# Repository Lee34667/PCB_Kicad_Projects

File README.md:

Contains some the PCB projects I have done using KiCad. Most of this boards have been used in the industries and research work.

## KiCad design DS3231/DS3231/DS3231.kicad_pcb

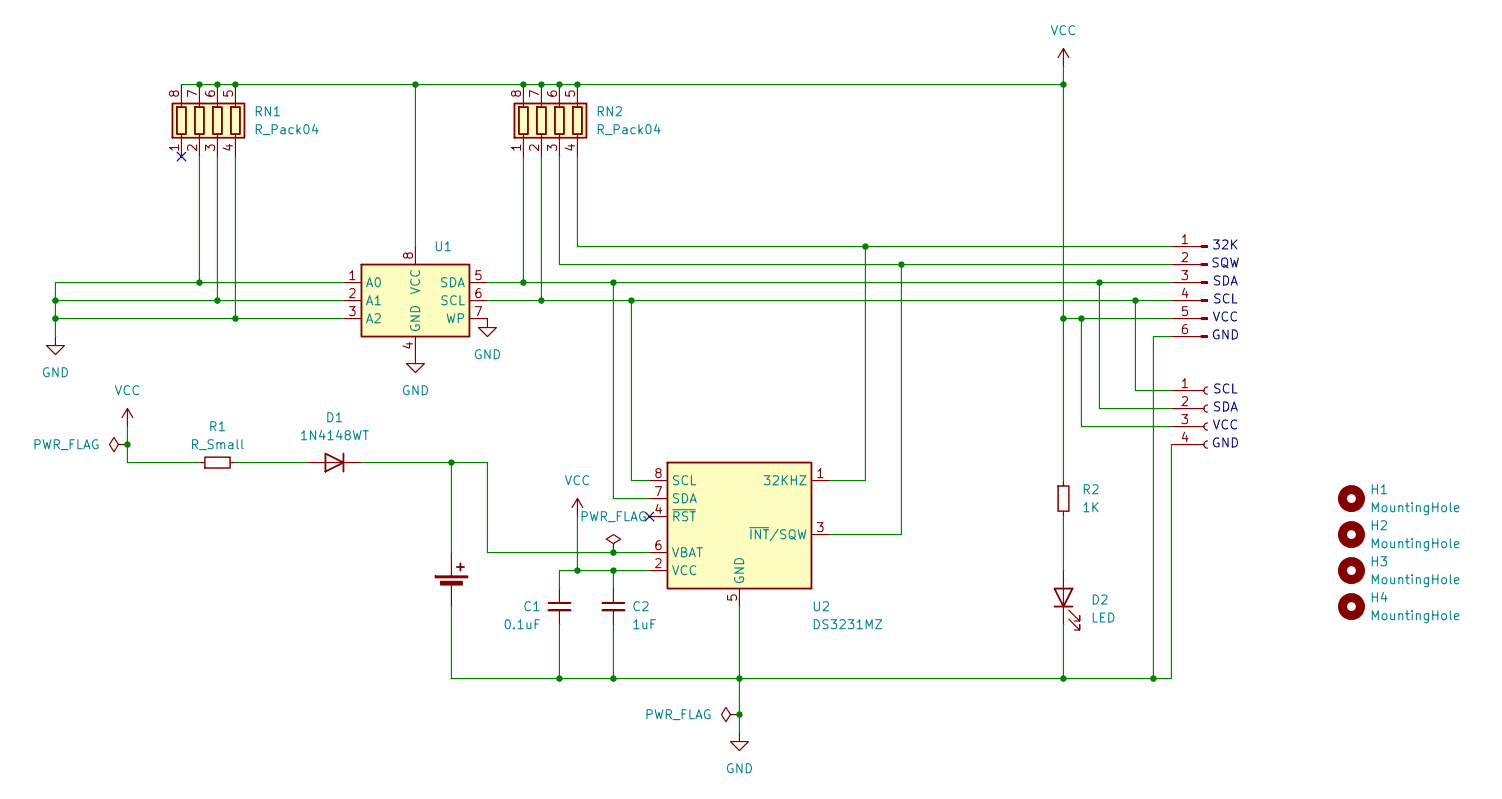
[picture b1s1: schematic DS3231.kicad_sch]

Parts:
BT1: Battery_Cell; BatteryHolder_Keystone_103_1x20mm
C1: 0.1uF; C_0805_2012Metric_Pad1.18x1.45mm_HandSolder
C2: 1uF; C_0805_2012Metric_Pad1.18x1.45mm_HandSolder
D1: 1N4148WT; D_1206_3216Metric_Pad1.42x1.75mm_HandSolder
D2: LED; LED_0805_2012Metric_Pad1.15x1.40mm_HandSolder
H1, H2, H3, H4: MountingHole; MountingHole_2.1mm
J1: Conn_01x06_Pin; PinHeader_1x06_P2.54mm_Horizontal
J2: Conn_01x04_Socket; PinHeader_1x04_P2.54mm_Vertical
R1: R_Small; R_0805_2012Metric_Pad1.20x1.40mm_HandSolder
R2: 1K; R_0805_2012Metric_Pad1.20x1.40mm_HandSolder
RN1, RN2: R_Pack04; R_Array_Convex_4x0603
U1: AT24CS32-SSHM; SOIC-8_3.9x4.9mm_P1.27mm
U2: DS3231MZ; SO-8_5.3x6.2mm_P1.27mm

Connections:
GND: BT1.2 (-), C1.2, C2.2, D2.1 (K), J1.6, J2.4, RN1.2 (R2.1), RN1.3 (R3.1), RN1.4 (R4.1), U1.1 (A0), U1.2 (A1), U1.3 (A2), U1.4 (GND), U1.7 (WP), U2.5 (GND)
unnamed: BT1.1 (+), D1.1 (K), U2.6 (VBAT)
unnamed: D1.2 (A), R1.2
unnamed: D2.2 (A), R2.2
unnamed: J1.1, RN2.4 (R4.1), U2.1 (32KHZ)
unnamed: J1.2, RN2.3 (R3.1), U2.3 (~INT/SQW)
unnamed: J1.3, J2.2, RN2.1 (R1.1), U1.5 (SDA), U2.7 (SDA)
unnamed: J1.4, J2.1, RN2.2 (R2.1), U1.6 (SCL), U2.8 (SCL)
VCC: C1.1, C2.1, J1.5, J2.3, R1.1, R2.1, RN1.5 (R4.2), RN1.6 (R3.2), RN1.7 (R2.2), RN1.8 (R1.2), RN2.5 (R4.2), RN2.6 (R3.2), RN2.7 (R2.2), RN2.8 (R1.2), U1.8 (VCC), U2.2 (VCC)

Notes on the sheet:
SCL
GND
SDA
VCC
SQW
VCC
32K
GND

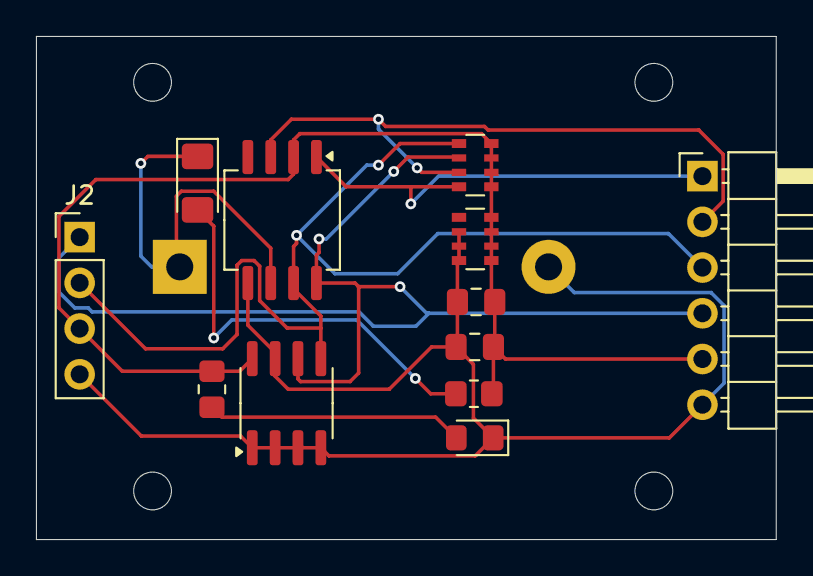
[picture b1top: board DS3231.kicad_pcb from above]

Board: 2 copper layers, 41.1 x 27.9 mm, 17 parts (1 on the bottom side), 9 nets.

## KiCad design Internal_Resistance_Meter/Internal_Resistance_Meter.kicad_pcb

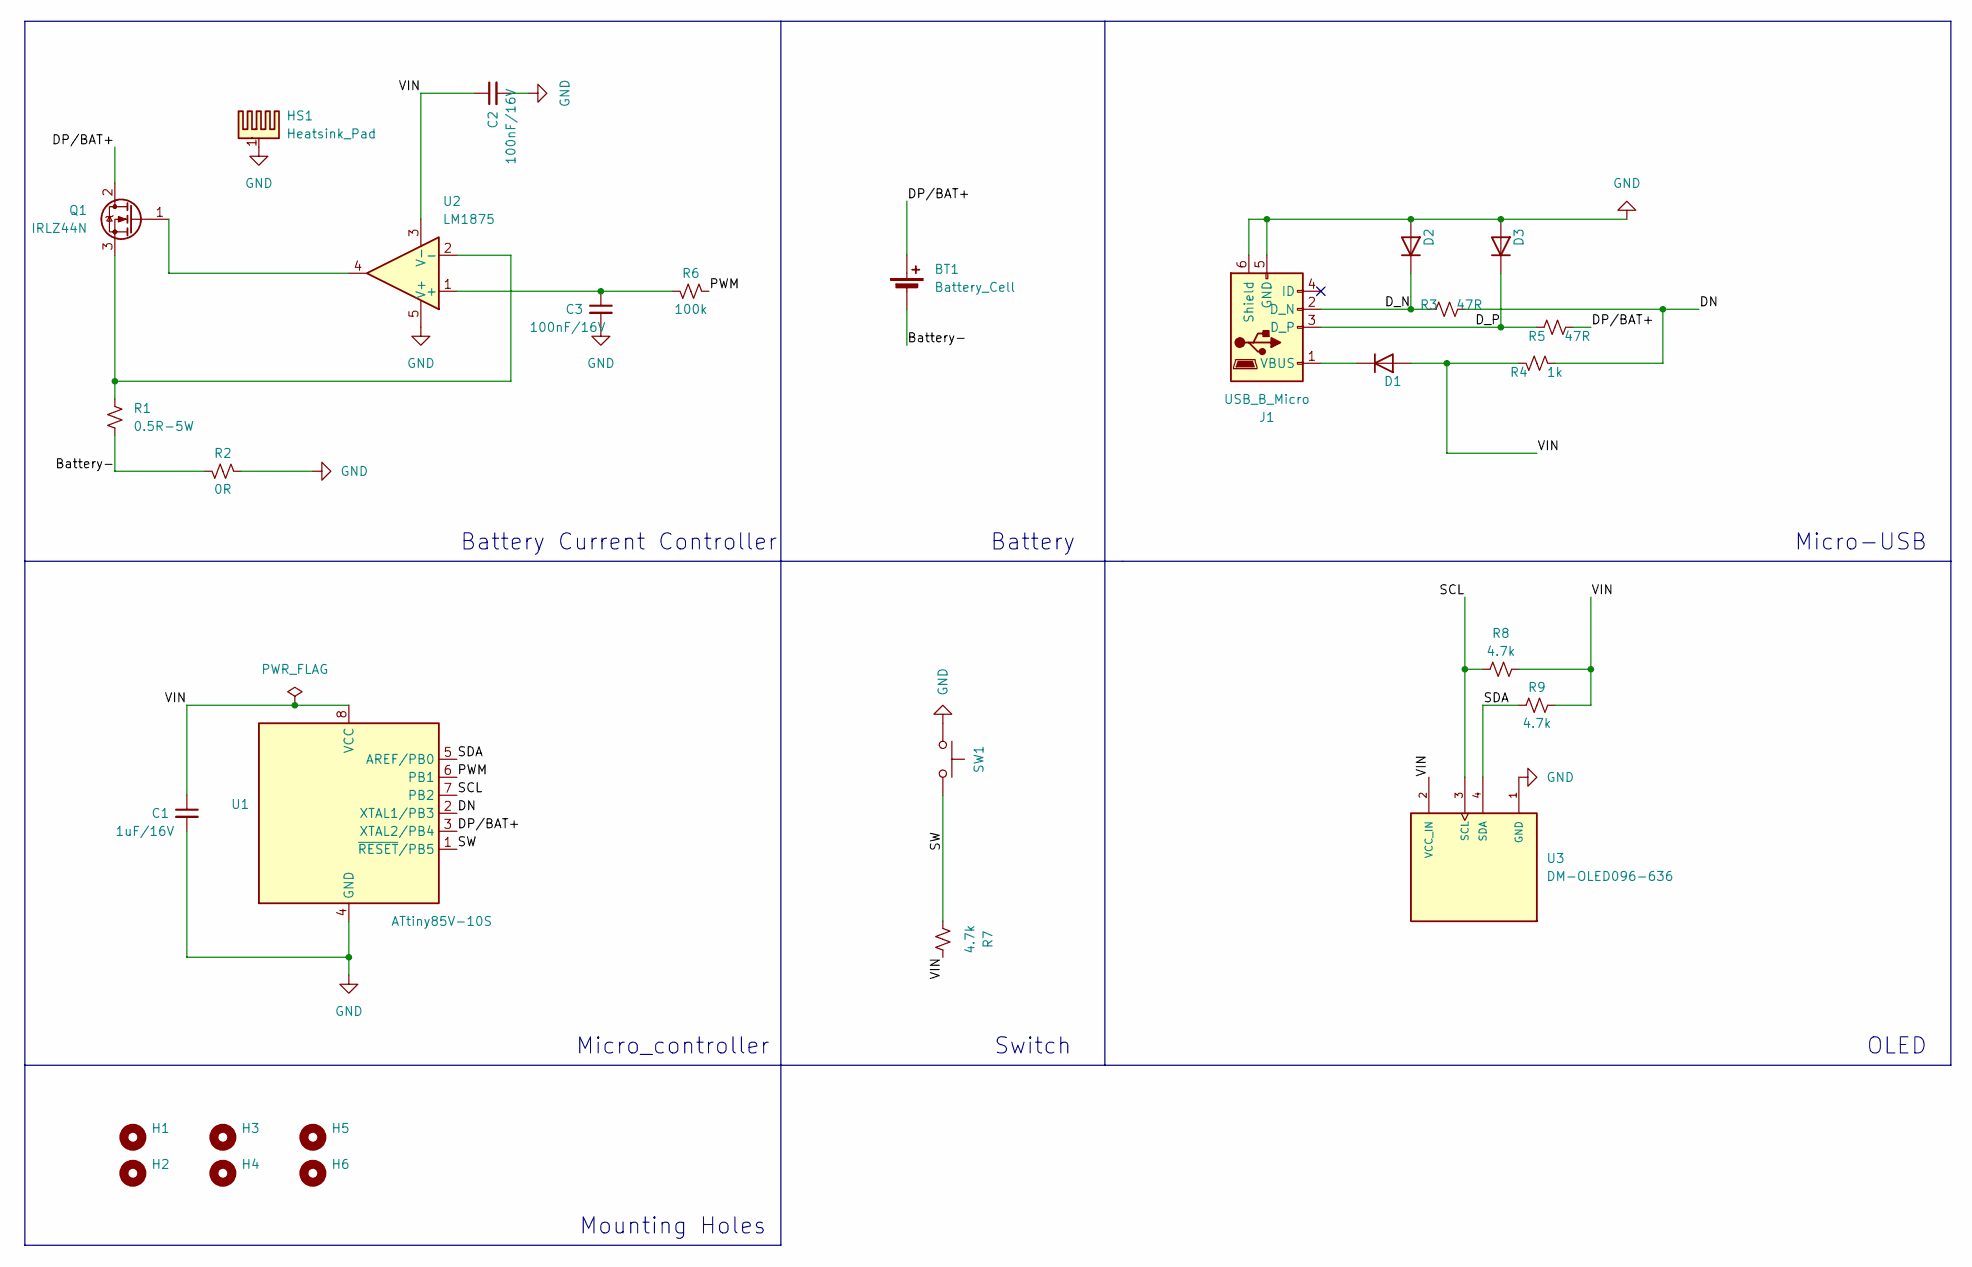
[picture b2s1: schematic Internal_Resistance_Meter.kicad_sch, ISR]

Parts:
BT1: Battery_Cell; BatteryHolder_MPD_BH-18650-PC2
C1: 1uF/16V; C_1210_3225Metric_Pad1.33x2.70mm_HandSolder
C2, C3: 100nF/16V; C_1210_3225Metric_Pad1.33x2.70mm_HandSolder
D1, D2, D3: 1N4148WT; D_SOD-523
H1, H2, H3, H4, H5, H6: MountingHole; MountingHole_2.1mm
HS1: Heatsink_Pad; HSINK_577202B04000G
J1: USB_B_Micro; USB_Micro-B_Molex_47346-0001
Q1: IRLZ44N; TO-92_Inline_W4.0mm_Horizontal_FlatSideDown
R1: 0.5R-5W; R_Axial_DIN0414_L11.9mm_D4.5mm_P15.24mm_Horizontal
R2: 0R; R_1210_3225Metric_Pad1.30x2.65mm_HandSolder
R3, R5: 47R; R_1210_3225Metric_Pad1.30x2.65mm_HandSolder
R4: 1k; R_1210_3225Metric_Pad1.30x2.65mm_HandSolder
R6: 100k; R_1210_3225Metric_Pad1.30x2.65mm_HandSolder
R7, R8, R9: 4.7k; R_1210_3225Metric_Pad1.30x2.65mm_HandSolder
SW1: SW_Push; SW_PUSH_6mm
U1: ATtiny85V-10S; SOIC-8_3.9x4.9mm_P1.27mm
U2: LM1875; SOT-23-5
U3: DM-OLED096-636; MODULE_DM-OLED096-636; PARTREV 2018-09-10

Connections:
/Battery-: BT1.2 (-), R1.2, R2.2
/DN: R3.1, R4.1, U1.2 (XTAL1/PB3)
/DP/BAT+: BT1.1 (+), Q1.2 (D), R5.1, U1.3 (XTAL2/PB4)
/D_N: D2.1 (K), J1.2 (D_N), R3.2
/D_P: D3.1 (K), J1.3 (D_P), R5.2
/PWM: R6.1, U1.6 (PB1)
/SCL: R8.1, U1.7 (PB2), U3.3 (SCL)
/SDA: R9.2, U1.5 (AREF/PB0), U3.4 (SDA)
/SW: R7.1, SW1.2, U1.1 (~RESET/PB5)
/VIN: C1.1, C2.1, D1.2 (A), R4.2, R7.2, R8.2, R9.1, U1.8 (VCC), U2.3 (V-), U3.2 (VCC_IN)
GND: C1.2, C2.2, C3.2, D2.2 (A), D3.2 (A), HS1.1, J1.5 (GND), J1.6 (Shield), R2.1, SW1.1, U1.4 (GND), U2.5 (V+), U3.1 (GND)
unnamed: D1.1 (K), J1.1 (VBUS)
unnamed: Q1.1 (G), U2.4
unnamed: Q1.3 (S), R1.1, U2.2 (-)
unnamed: C3.1, R6.2, U2.1 (+)

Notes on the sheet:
Switch
Battery
OLED
Battery Current Controller
Mounting Holes
Micro-USB
Micro_controller

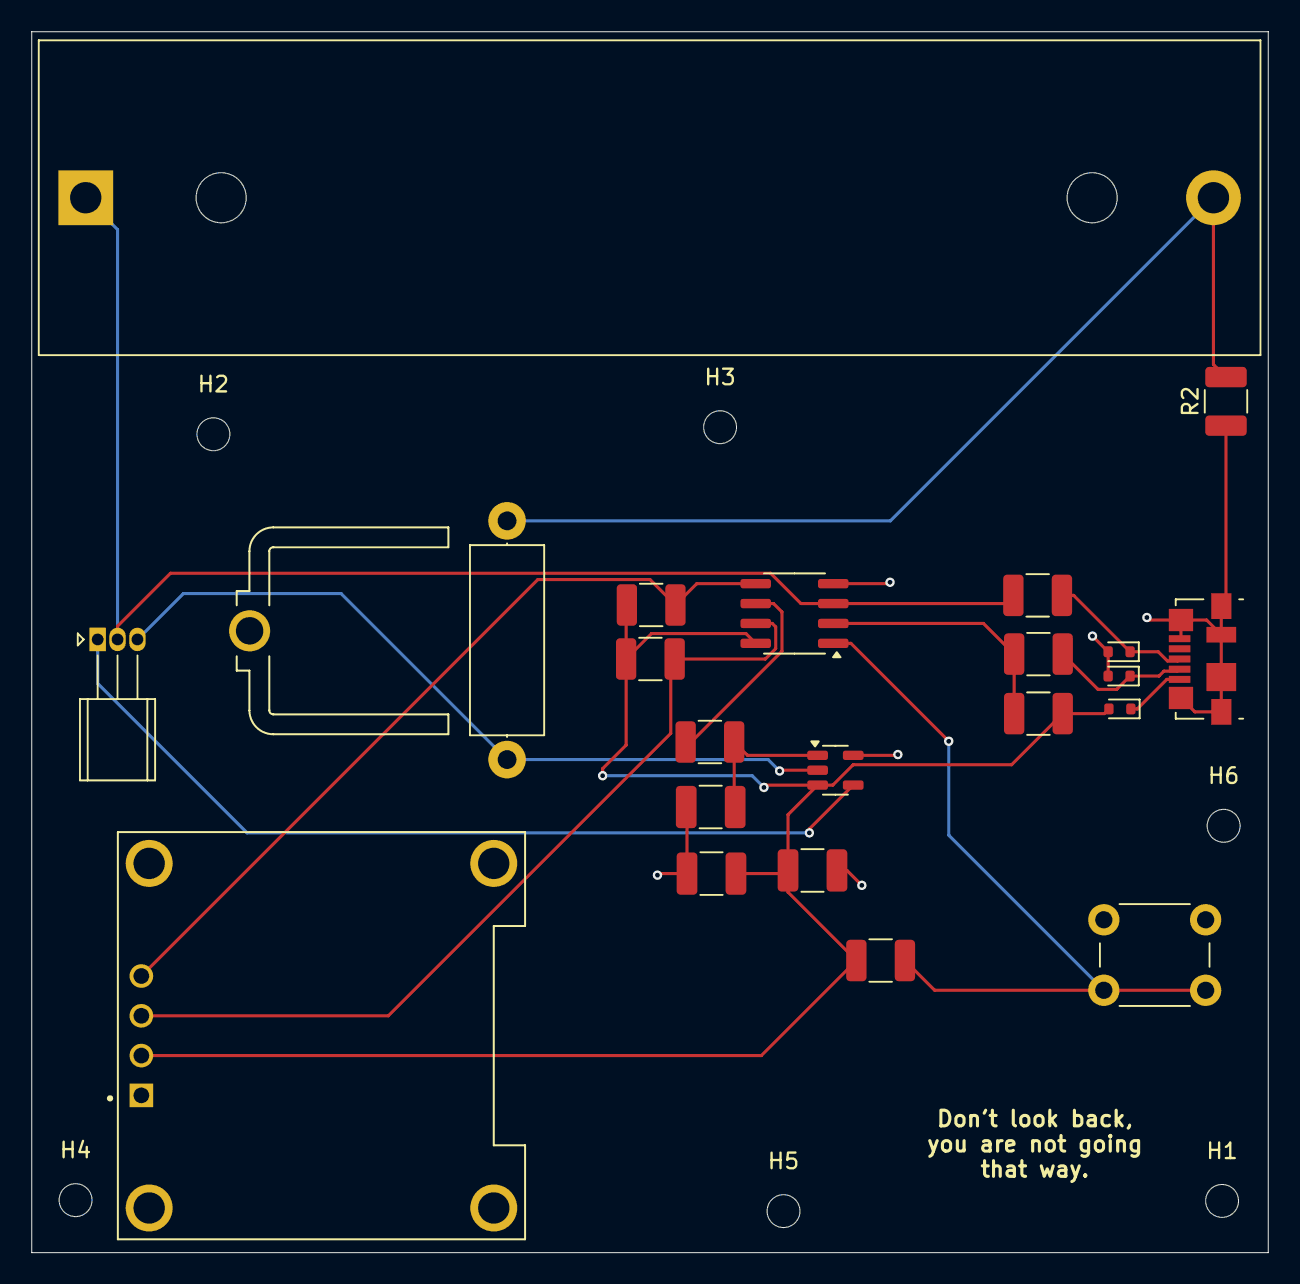
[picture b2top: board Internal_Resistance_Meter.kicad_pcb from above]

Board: 2 copper layers, 79.0 x 78.0 mm, 29 parts (0 on the bottom side), 15 nets.

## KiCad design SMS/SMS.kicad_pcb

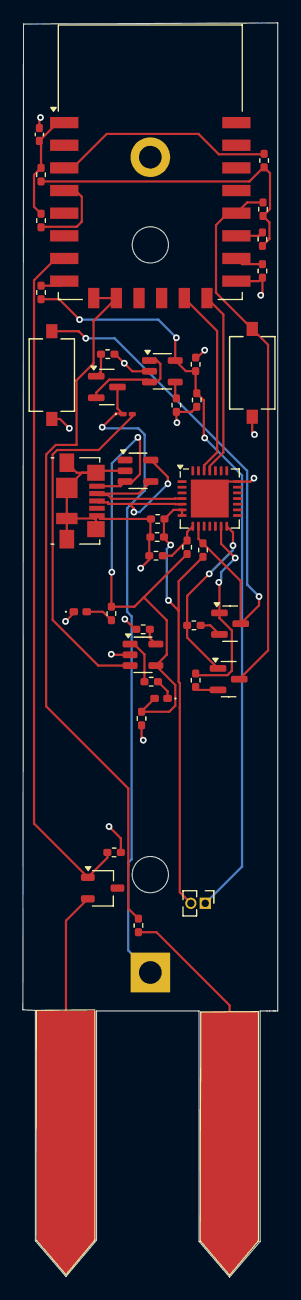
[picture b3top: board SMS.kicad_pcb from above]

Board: 2 copper layers, 22.5 x 110.8 mm, 42 parts (1 on the bottom side), 33 nets.

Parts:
BT1: Battery_Cell; BatteryHolder_MPD_BH-18650-PC2
C1: 0.1uF/6.3V; C_0402_1005Metric_Pad0.74x0.62mm_HandSolder
C2, C3: 2.2uF/6.3V; R_0402_1005Metric_Pad0.72x0.64mm_HandSolder
C4: 10uF; R_0402_1005Metric_Pad0.72x0.64mm_HandSolder
C5: 0.1uF/50V; R_0402_1005Metric_Pad0.72x0.64mm_HandSolder
C6, C7: 10uF/6.3V; R_0402_1005Metric_Pad0.72x0.64mm_HandSolder
C8: 0.1uF/6.3V; R_0402_1005Metric_Pad0.72x0.64mm_HandSolder
D1, D2: RED; LED_0402_1005Metric_Pad0.77x0.64mm_HandSolder
D3: ESDA14V2SC5; SOT-23-5
D4: SS14; D_0201_0603Metric_Pad0.64x0.40mm_HandSolder
J1: USB_B_Micro; USB_Micro-B_Molex_47346-0001
J2: Conn_01x02_Pin; PinHeader_1x02_P1.27mm_Vertical
Q1: 2N3904; TSOT-23
Q2: Si2319CDS; SOT-23
Q3, Q4: SS8050CTA; SOT-23
R1, R2, R3, R4, R5, R10, R11: 12k; R_0402_1005Metric_Pad0.72x0.64mm_HandSolder
R6: 0R; R_0402_1005Metric_Pad0.72x0.64mm_HandSolder
R7: 680R; R_0402_1005Metric_Pad0.72x0.64mm_HandSolder
R8: 330R; R_0402_1005Metric_Pad0.72x0.64mm_HandSolder
R9: 1.25k; R_0402_1005Metric_Pad0.72x0.64mm_HandSolder
R12: 100k; R_0402_1005Metric_Pad0.72x0.64mm_HandSolder
R13: 22.1k; R_0402_1005Metric_Pad0.72x0.64mm_HandSolder
R14, R17: 47.5k; R_0402_1005Metric_Pad0.72x0.64mm_HandSolder
R15, R16: 10k; R_0402_1005Metric_Pad0.72x0.64mm_HandSolder
SW1, SW2: SW_Push; SW_Tactile_SPST_NO_Straight_CK_PTS636Sx25SMTRLFS
U1: ESP-12E
U2: LTC4054ES5-4.2; TSOT-23-5
U3: CP2102N-Axx-xQFN28; QFN-28-1EP_5x5mm_P0.5mm_EP3.35x3.35mm
U4: MIC5219-3.3YM5; SOT-23-5

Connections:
+3.3V: C2.2, C7.1, C8.1, J2.1, U4.5 (OUT)
/DTR: Q4.1, R15.2, U3.14 (~DTR)
/GPIO2: R2.2, U1.17 (GPIO2)
/GPIO15: R5.1, U1.16 (GPIO15)
/GPIO16: C1.1, R4.2, R6.1, U1.1 (~RST)
/RTS: Q3.1, R16.2, U3.13 (~RTS)
/USB_DN: D3.4 (K), J1.2 (D-), U3.4 (D+)
/USB_DP: D3.5 (K), J1.3 (D+), U3.5 (D-)
/VBUS_DEV: R13.1, R14.2, U3.8 (VBUS)
CHARGER: D4.2 (A), U2.3 (BAT)
CP2102-PWR: C4.1, C5.1, J2.2, R17.1, U3.6 (VDD), U3.7 (VREGIN)
GND: BT1.2 (-), C1.2, C3.1, C4.2, C5.2, C6.2, C7.2, C8.2, D1.1 (K), D3.2 (A), J1.5 (GND), J1.6 (Shield), R5.2, R9.2, R10.1, R12.1, R14.1, SW1.1, SW2.1, U1.15 (GND), U2.2 (GND), U3.21 (GND), U3.29 (GND), U4.2 (GND)
GPIO0: Q4.3, R1.2, SW1.2, U1.18 (GPIO0)
unnamed: BT1.1 (+), D4.1 (K), Q2.3 (D)
unnamed: D1.2 (A), R7.1
unnamed: D2.1 (K), R8.1
unnamed: Q2.1 (G), R12.2
unnamed: Q2.2 (S), U4.1 (IN), U4.3 (EN)
unnamed: Q3.2, R15.1
unnamed: Q4.2, R16.1
unnamed: R1.1, R2.1, R3.1, R4.1
unnamed: R3.2, U1.3 (EN)
unnamed: R6.2, U1.4 (GPIO16)
unnamed: C2.1, U1.8 (VCC)
unnamed: R9.1, U2.5 (PROG)
unnamed: R8.2, U2.1 (~CHRG)
unnamed: C6.1, U4.4 (BP)
PROBE_PWR: Q1.3 (C), R11.2, U1.9 (GPI04), U1.10 (GPI05)
RST: Q3.3, R17.2, SW2.2, U3.9 (~RST)
RX: U1.14 (RXD), U3.25 (RXD)
SIG: Q1.1 (E), R10.2, U1.7 (ADC)
TX: U1.13 (TXD), U3.26 (TXD)
VBUS: C3.2, D2.2 (A), D3.3 (K), J1.1 (VBUS), R7.2, R13.2, U2.4 (V_{CC})

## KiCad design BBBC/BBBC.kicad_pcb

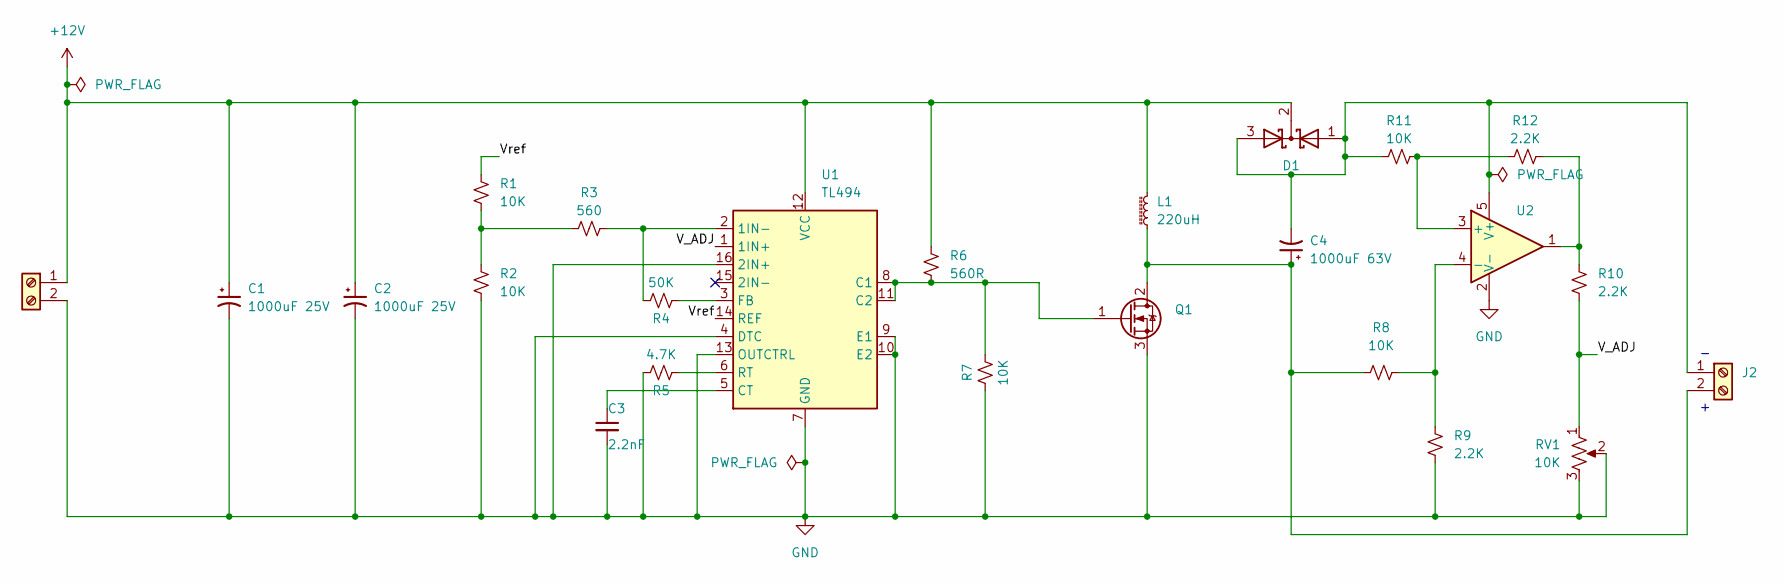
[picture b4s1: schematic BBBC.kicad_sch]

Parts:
C1, C2: 1000uF 25V; C_Radial_D4.0mm_H7.0mm_P1.50mm
C3: 2.2nF; C_Rect_L4.6mm_W2.0mm_P2.50mm_MKS02_FKP02
C4: 1000uF 63V; C_Radial_D5.0mm_H11.0mm_P2.00mm
D1: D_Schottky_Dual_CommonCathode_AKA; SOT96P240X120-3N
J1, J2: Screw_Terminal_01x02; TerminalBlock_Phoenix_MKDS-1,5-2-5.08_1x02_P5.08mm_Horizont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
L1: 220uH; LairdTech_28C0236-0JW-10
Q1: IRF540N; TO-220-3_Vertical
R1, R2, R7, R8, R11: 10K; R_Axial_DIN0204_L3.6mm_D1.6mm_P5.08mm_Horizontal
R3: 560; R_Axial_DIN0204_L3.6mm_D1.6mm_P5.08mm_Horizontal
R4: 50K; R_Axial_DIN0204_L3.6mm_D1.6mm_P5.08mm_Horizontal
R5: 4.7K; R_Axial_DIN0204_L3.6mm_D1.6mm_P5.08mm_Horizontal
R6: 560R; R_Axial_DIN0204_L3.6mm_D1.6mm_P5.08mm_Horizontal
R9, R10, R12: 2.2K; R_Axial_DIN0204_L3.6mm_D1.6mm_P5.08mm_Horizontal
RV1: 10K; Potentiometer_Bourns_3299Y_Vertical
U1: TL494; DIP794W45P254L1969H508Q16
U2: ADA4610-1xRJ; SOT-23-5

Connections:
+12V: C1.1, C2.1, D1.2 (K), J1.1, L1.2, R6.1, U1.12 (VCC)
/V_ADJ: R10.1, RV1.1, U1.1 (1IN+)
/Vref: R1.2, U1.14 (REF)
GND: C1.2, C2.2, C3.2, J1.2, Q1.3 (S), R2.1, R5.1, R7.2, R9.1, RV1.2, RV1.3, U1.4 (DTC), U1.7 (GND), U1.9 (E1), U1.10 (E2), U1.13 (OUTCTRL), U1.16 (2IN+), U2.2 (V-)
unnamed: C4.2, D1.1 (A), D1.3 (A), J2.1, R11.1, U2.5 (V+)
unnamed: C4.1, J2.2, L1.1, Q1.2 (D), R8.1
unnamed: Q1.1 (G), R6.2, R7.1, U1.8 (C1), U1.11 (C2)
unnamed: R1.1, R2.2, R3.1
unnamed: R10.2, R12.1, U2.1
unnamed: R3.2, R4.1, U1.2 (1IN-)
unnamed: C3.1, U1.5 (CT)
unnamed: R4.2, U1.3 (FB)
unnamed: R5.2, U1.6 (RT)
unnamed: R11.2, R12.2, U2.3 (+)
unnamed: R8.2, R9.2, U2.4 (-)

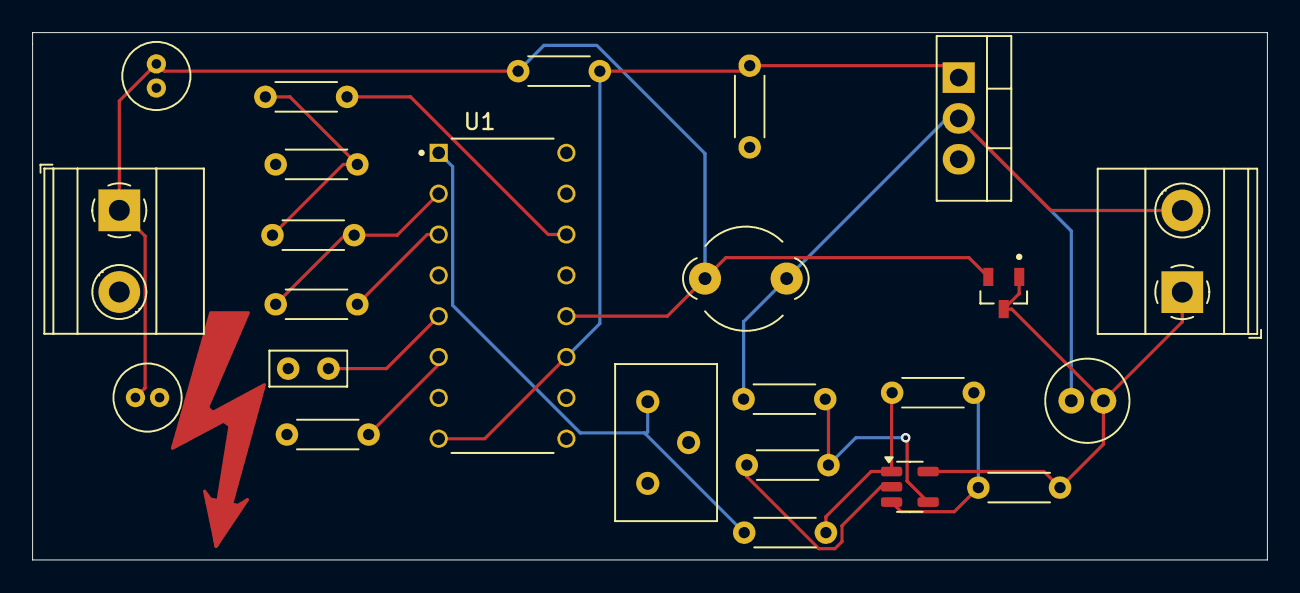
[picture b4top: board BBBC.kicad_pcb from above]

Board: 2 copper layers, 76.8 x 32.8 mm, 24 parts (0 on the bottom side), 15 nets.

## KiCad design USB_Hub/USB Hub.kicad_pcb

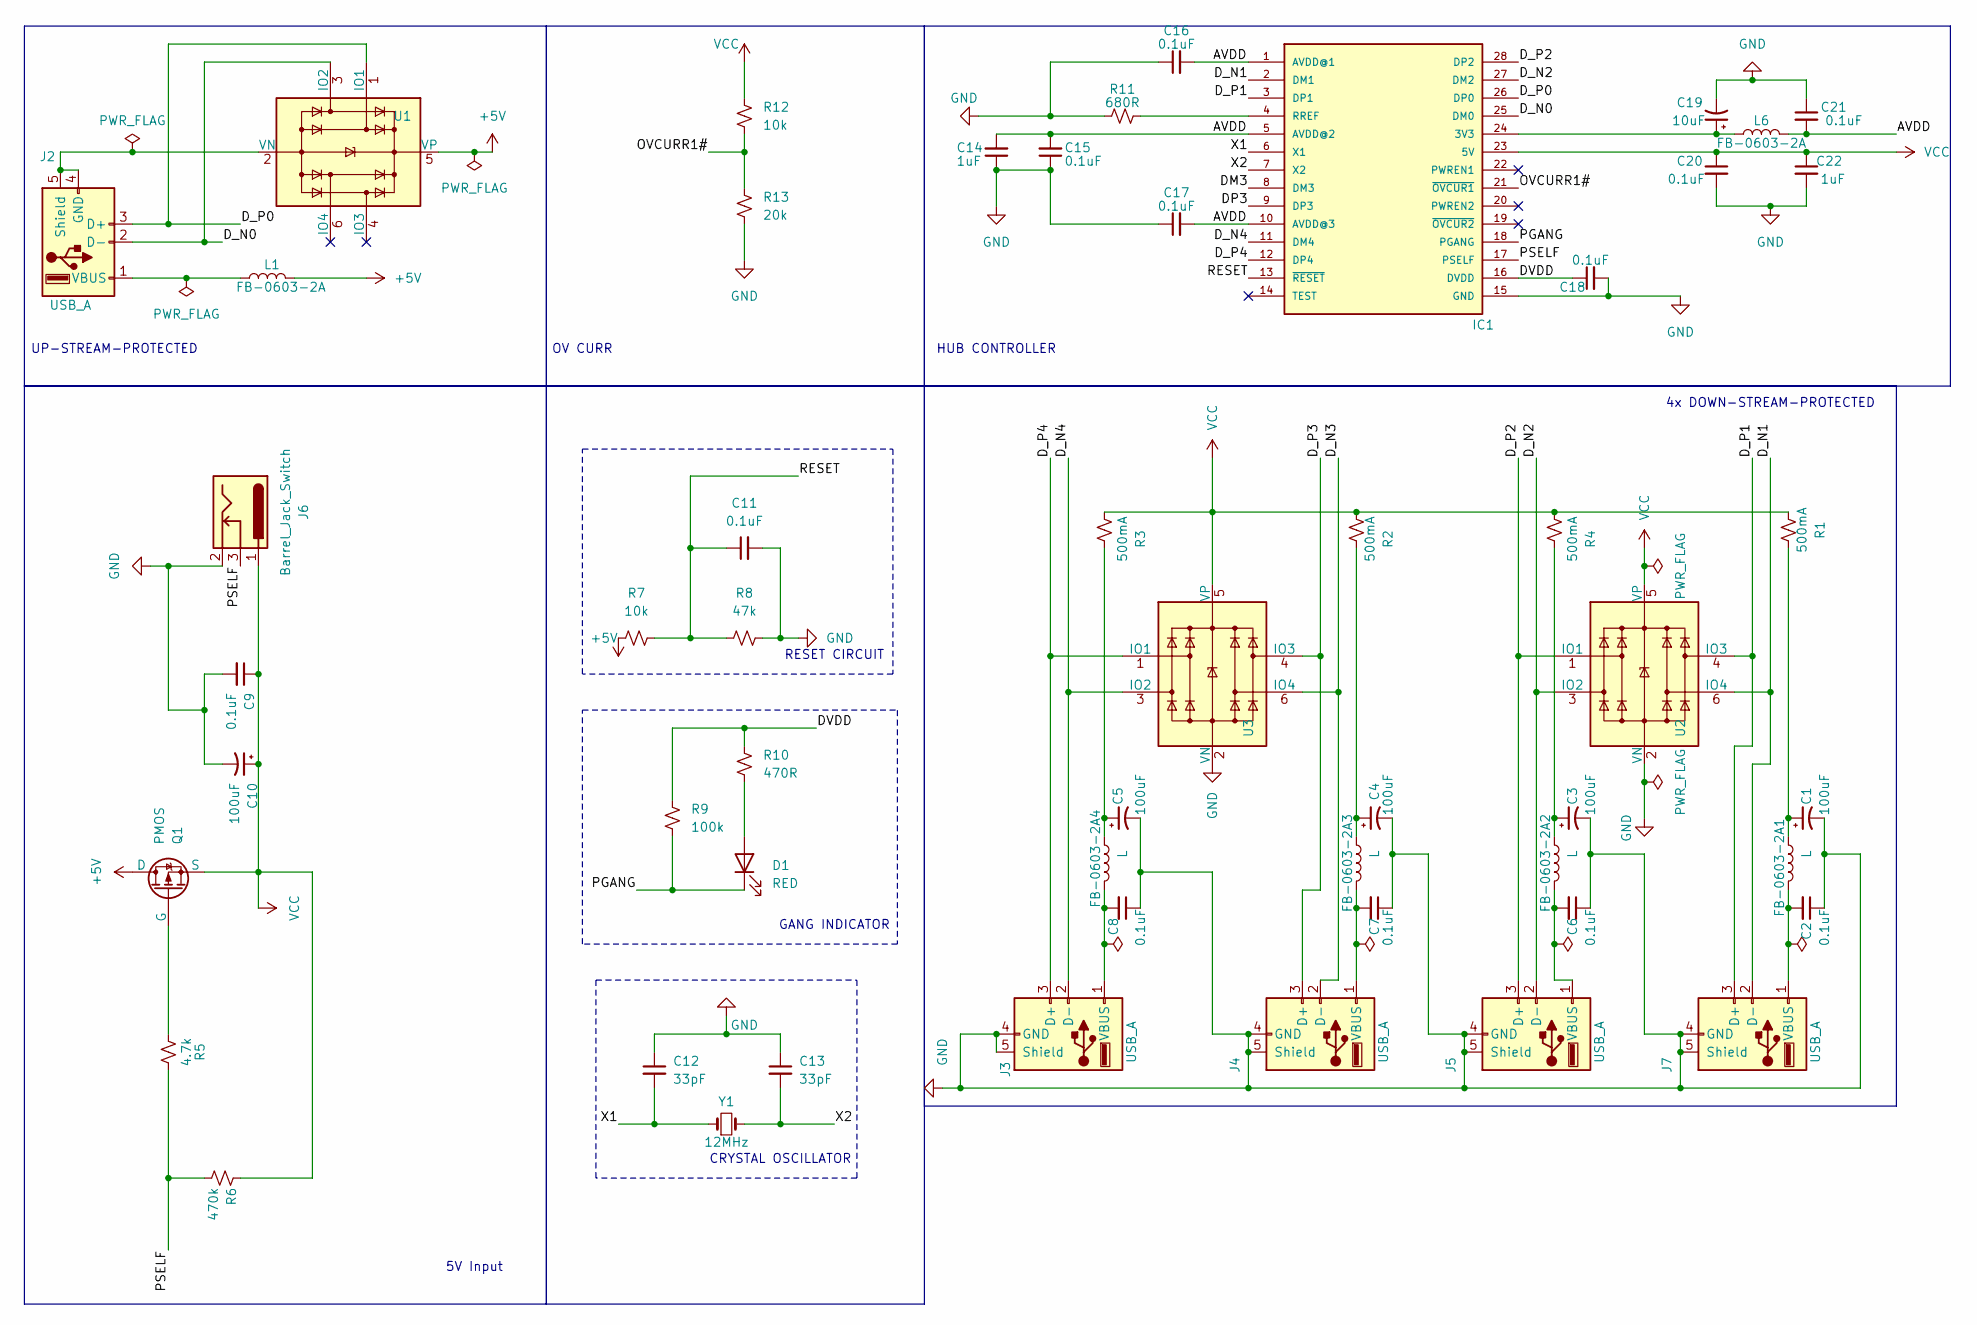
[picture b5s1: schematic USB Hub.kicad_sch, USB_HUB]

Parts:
C1, C3, C4: 100uF; C_Radial_D4.0mm_H7.0mm_P1.50mm
C2, C6, C7, C8, C9, C11, C15, C16, C17, C18, C20, C21: 0.1uF; C_0805_2012Metric_Pad1.18x1.45mm_HandSolder
C5, C10: 100uF; CP_Radial_D8.0mm_P3.80mm
C12, C13: 33pF; C_0805_2012Metric_Pad1.18x1.45mm_HandSolder
C14, C22: 1uF; C_0805_2012Metric_Pad1.18x1.45mm_HandSolder
C19: 10uF; CP_Radial_D8.0mm_P3.80mm
D1: RED; LED_0805_2012Metric_Pad1.15x1.40mm_HandSolder
FB-0603-2A1, FB-0603-2A2, FB-0603-2A3, FB-0603-2A4: L; L_0805_2012Metric_Pad1.15x1.40mm_HandSolder
IC1: GL850G; 28SSOP
J2: USB_A; USB_A_CNCTech_1001-011-01101_Horizontal
J3, J4, J5, J7: USB_A; USB_A_Molex_67643_Horizontal
J6: Barrel_Jack_Switch; BarrelJack_Horizontal
L1, L6: FB-0603-2A; L_0805_2012Metric_Pad1.15x1.40mm_HandSolder
Q1: PMOS; SOT95P240X110-3N
R1, R2, R3, R4: 500mA; R_0805_2012Metric_Pad1.20x1.40mm_HandSolder
R5: 4.7k; R_0805_2012Metric_Pad1.20x1.40mm_HandSolder
R6: 470k; R_0805_2012Metric_Pad1.20x1.40mm_HandSolder
R7, R12: 10k; R_0805_2012Metric_Pad1.20x1.40mm_HandSolder
R8: 47k; R_0805_2012Metric_Pad1.20x1.40mm_HandSolder
R9: 100k; R_0805_2012Metric_Pad1.20x1.40mm_HandSolder
R10: 470R; R_0805_2012Metric_Pad1.20x1.40mm_HandSolder
R11: 680R; R_0805_2012Metric_Pad1.20x1.40mm_HandSolder
R13: 20k; R_0805_2012Metric_Pad1.20x1.40mm_HandSolder
U1, U2, U3: SRV05-4; SOT-23-6
Y1: 12MHz; Crystal_HC49-4H_Vertical

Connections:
+5V: L1.2, Q1.1 (D), R7.1, U1.5 (VP)
/AVDD: C14.2, C15.2, C16.2, C17.2, C21.2, IC1.1 (AVDD@1), IC1.5 (AVDD@2), IC1.10 (AVDD@3), L6.2
/DM3: IC1.8 (DM3)
/DP3: IC1.9 (DP3)
/DVDD: C18.1, IC1.16 (DVDD), R9.1, R10.1
/D_N0: IC1.25 (DM0), J2.2 (D-), U1.3 (IO2)
/D_N1: IC1.2 (DM1), J7.2 (D-), U2.6 (IO4)
/D_N2: IC1.27 (DM2), J5.2 (D-), U2.3 (IO2)
/D_N3: J4.2 (D-), U3.6 (IO4)
/D_N4: IC1.11 (DM4), J3.2 (D-), U3.3 (IO2)
/D_P0: IC1.26 (DP0), J2.3 (D+), U1.1 (IO1)
/D_P1: IC1.3 (DP1), J7.3 (D+), U2.4 (IO3)
/D_P2: IC1.28 (DP2), J5.3 (D+), U2.1 (IO1)
/D_P3: J4.3 (D+), U3.4 (IO3)
/D_P4: IC1.12 (DP4), J3.3 (D+), U3.1 (IO1)
/OVCURR1#: IC1.21 (~OVCUR1), R12.2, R13.1
/PGANG: D1.1 (K), IC1.18 (PGANG), R9.2
/PSELF: IC1.17 (PSELF), J6.3, R5.2, R6.1
/RESET: C11.1, IC1.13 (~RESET), R7.2, R8.1
/X1: C12.2, IC1.6 (X1), Y1.1
/X2: C13.2, IC1.7 (X2), Y1.2
GND: C1.2, C2.1, C3.2, C4.2, C5.2, C6.1, C7.1, C8.1, C9.2, C10.2, C11.2, C12.1, C13.1, C14.1, C15.1, C16.1, C17.1, C18.2, C19.2, C20.2, C21.1, C22.2, IC1.15 (GND), J3.4 (GND), J3.5 (Shield), J4.4 (GND), J4.5 (Shield), J5.4 (GND), J5.5 (Shield), J6.2, J7.4 (GND), J7.5 (Shield), R8.2, R11.1, R13.2, U2.2 (VN), U3.2 (VN)
unnamed: C1.1, FB-0603-2A1.1, R1.2
unnamed: C3.1, FB-0603-2A2.1, R4.2
unnamed: C4.1, FB-0603-2A3.1, R2.2
unnamed: C5.1, FB-0603-2A4.1, R3.2
unnamed: D1.2 (A), R10.2
unnamed: C19.1, IC1.24 (3V3), L6.1
unnamed: IC1.4 (RREF), R11.2
unnamed: J2.4 (GND), J2.5 (Shield), U1.2 (VN)
unnamed: J2.1 (VBUS), L1.1
unnamed: C8.2, FB-0603-2A4.2, J3.1 (VBUS)
unnamed: C7.2, FB-0603-2A3.2, J4.1 (VBUS)
unnamed: C6.2, FB-0603-2A2.2, J5.1 (VBUS)
unnamed: C2.2, FB-0603-2A1.2, J7.1 (VBUS)
unnamed: Q1.2 (G), R5.1
VCC: C9.1, C10.1, C20.1, C22.1, IC1.23 (5V), J6.1, Q1.3 (S), R1.1, R2.1, R3.1, R4.1, R6.2, R12.1, U2.5 (VP), U3.5 (VP)

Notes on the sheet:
5V Input
RESET CIRCUIT
HUB CONTROLLER
UP-STREAM-PROTECTED
GANG INDICATOR
CRYSTAL OSCILLATOR
4x DOWN-STREAM-PROTECTED
OV CURR

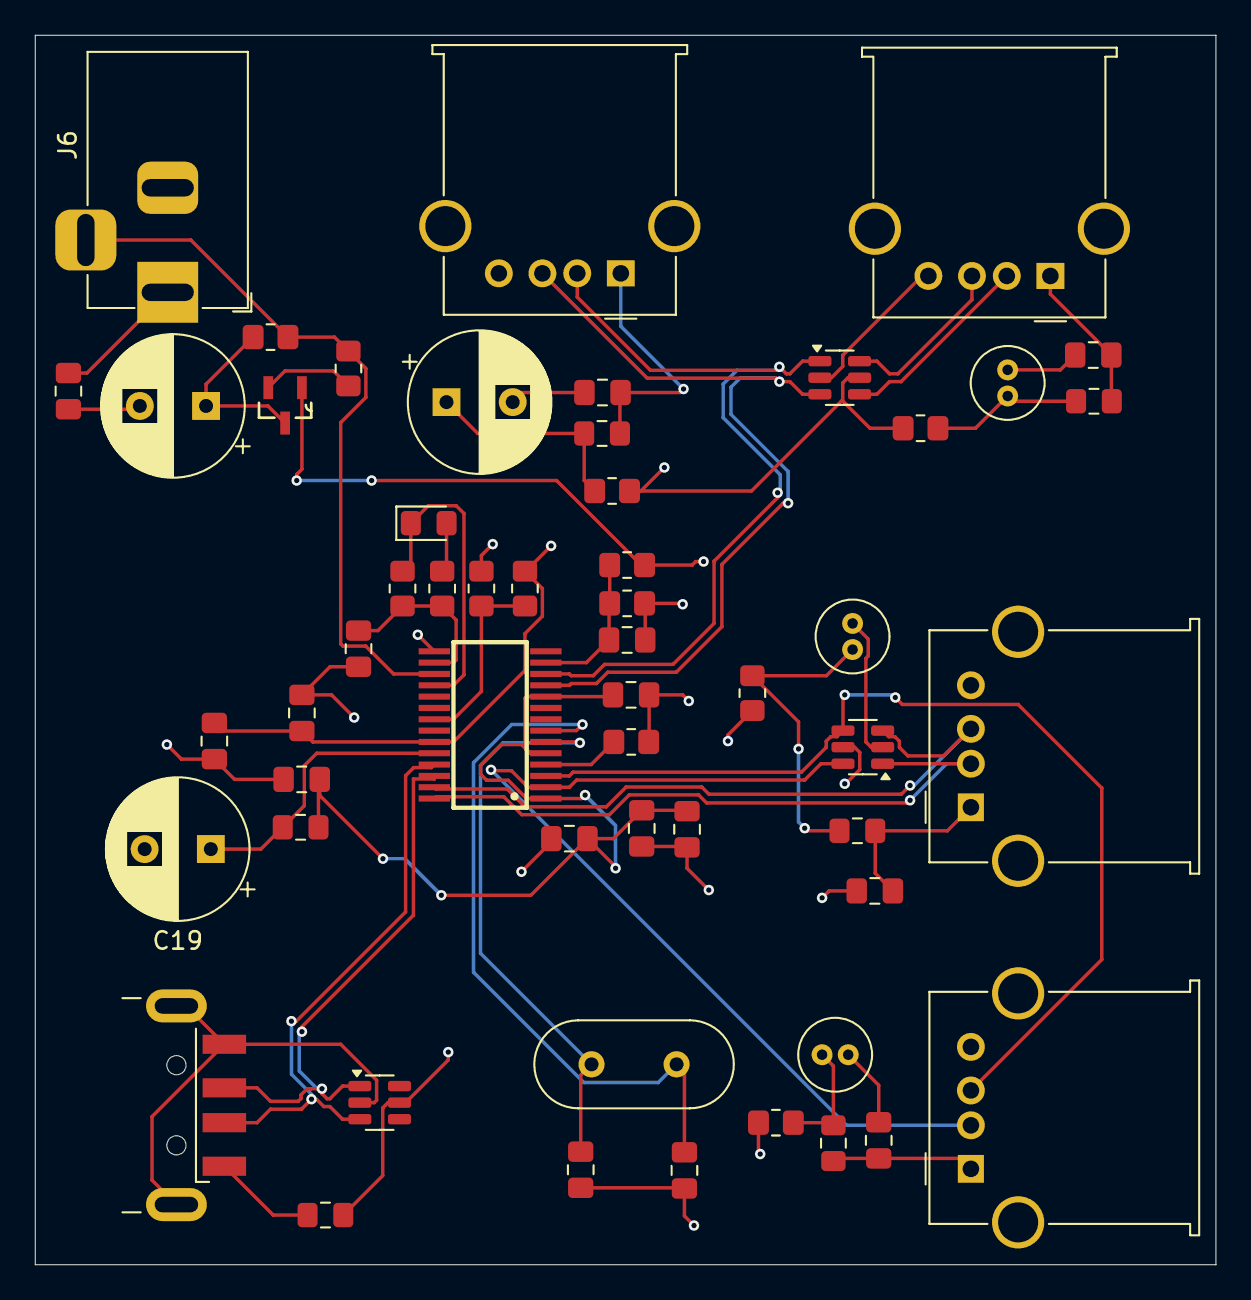
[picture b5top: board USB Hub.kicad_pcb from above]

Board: 4 copper layers, 67.8 x 70.5 mm, 54 parts (0 on the bottom side), 35 nets.
